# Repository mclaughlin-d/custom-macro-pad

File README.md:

# custom-macro-pad
This repo has a pretty simple PCB I made a while back, just to familiarize myself with KiCad. 
Here are some photos!

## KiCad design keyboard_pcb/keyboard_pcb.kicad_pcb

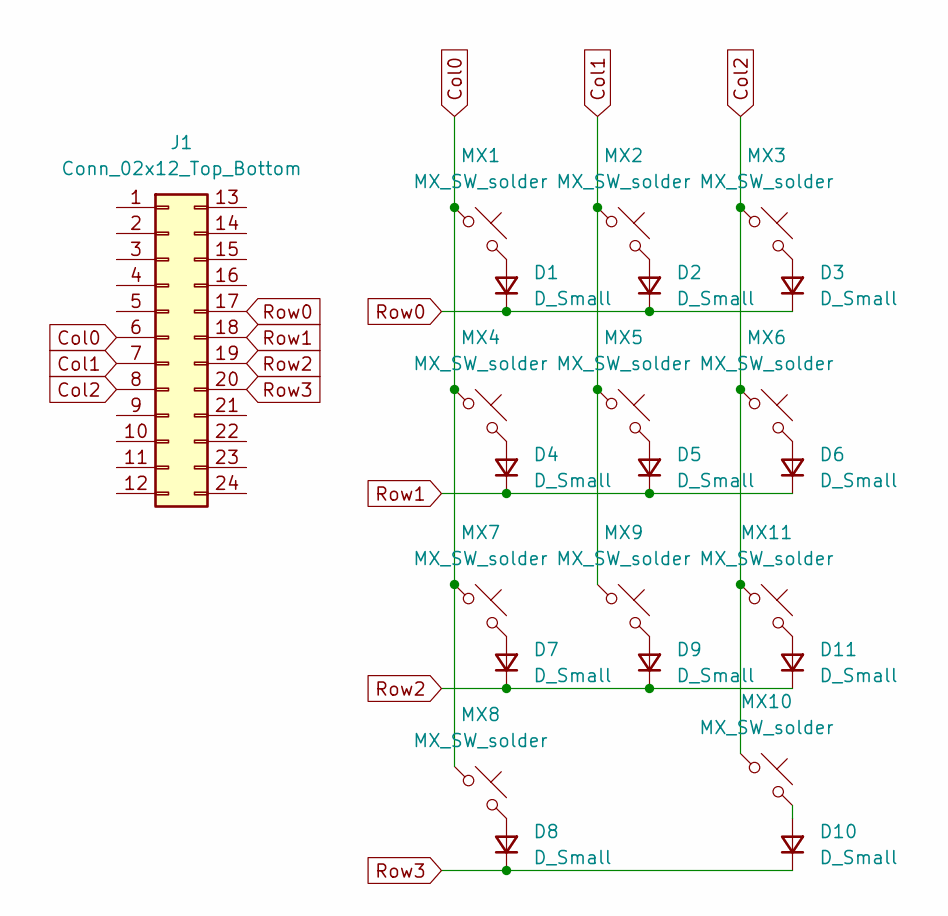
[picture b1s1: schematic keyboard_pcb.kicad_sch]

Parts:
D1, D2, D3, D4, D5, D6, D7, D8, D9, D10, D11: D_Small; D_SOD-123
J1: Conn_02x12_Top_Bottom; ProMicro_USBup
MX1, MX2, MX3, MX4, MX5, MX6, MX7, MX9, MX11: MX_SW_solder; SW_MX_1u
MX8, MX10: MX_SW_solder; SW_MX_1.5u

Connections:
Col0: J1.6, MX1.1, MX4.1, MX7.1, MX8.1
Col1: J1.7, MX2.1, MX5.1, MX9.1
Col2: J1.8, MX3.1, MX6.1, MX10.1, MX11.1
unnamed: D1.2 (A), MX1.2
unnamed: D2.2 (A), MX2.2
unnamed: D3.2 (A), MX3.2
unnamed: D4.2 (A), MX4.2
unnamed: D5.2 (A), MX5.2
unnamed: D6.2 (A), MX6.2
unnamed: D7.2 (A), MX7.2
unnamed: D8.2 (A), MX8.2
unnamed: D9.2 (A), MX9.2
unnamed: D10.2 (A), MX10.2
unnamed: D11.2 (A), MX11.2
Row0: D1.1 (K), D2.1 (K), D3.1 (K), J1.17
Row1: D4.1 (K), D5.1 (K), D6.1 (K), J1.18
Row2: D7.1 (K), D9.1 (K), D11.1 (K), J1.19
Row3: D8.1 (K), D10.1 (K), J1.20

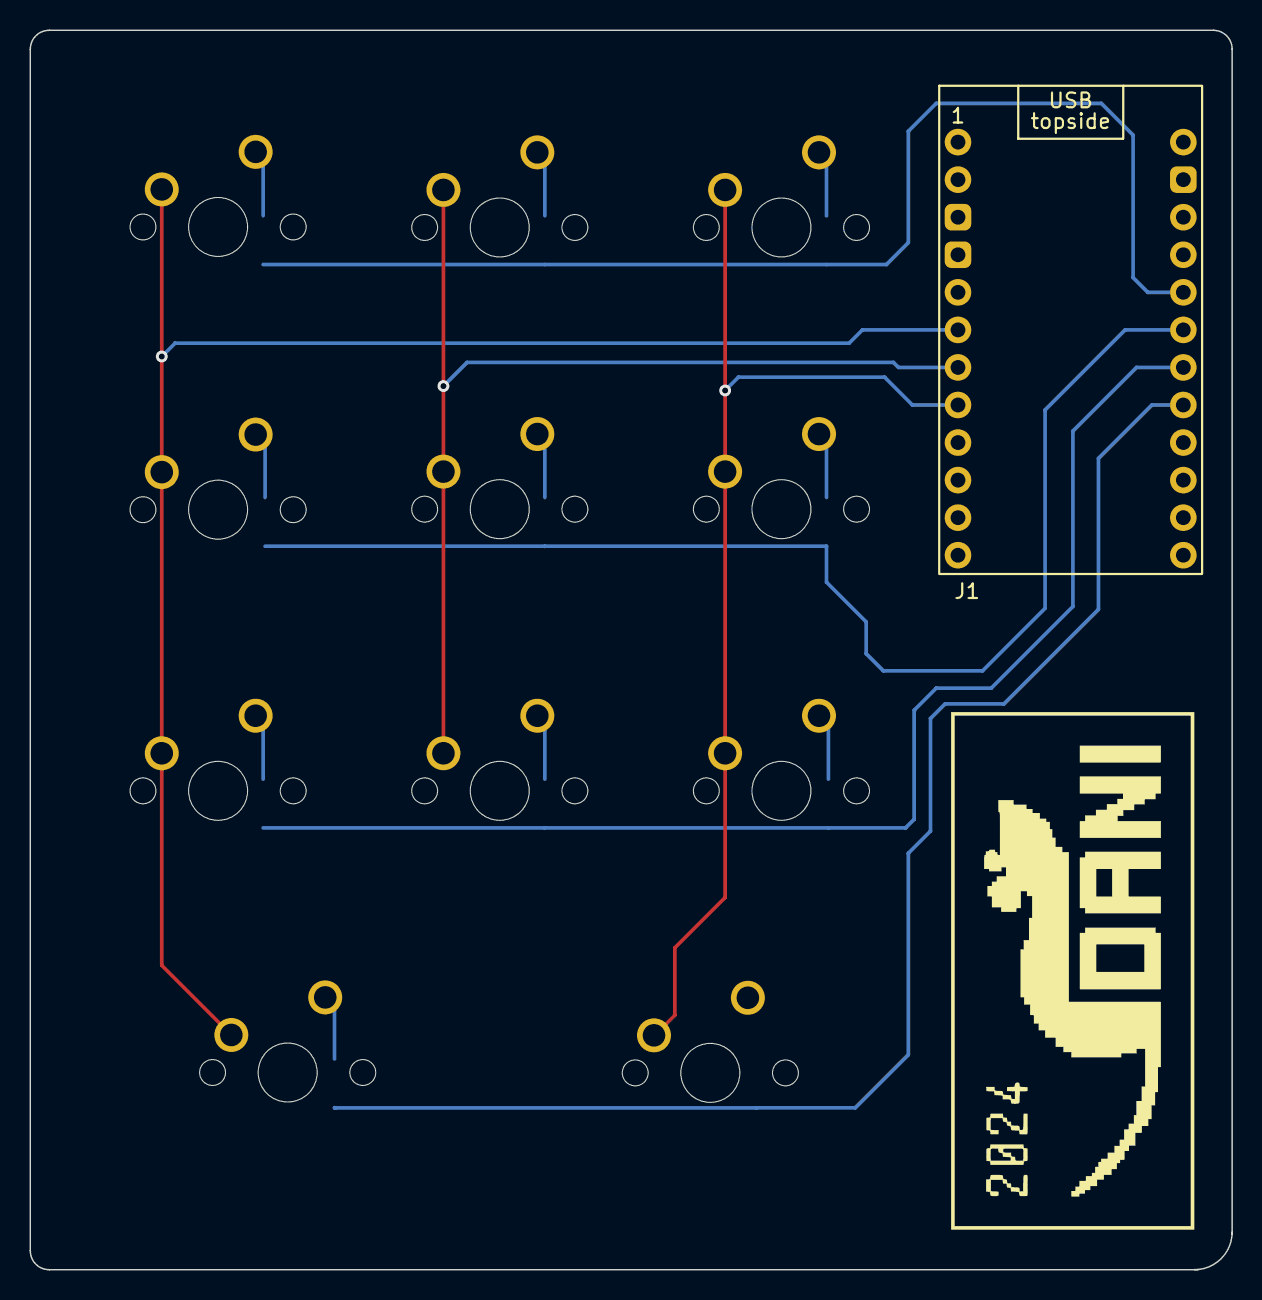
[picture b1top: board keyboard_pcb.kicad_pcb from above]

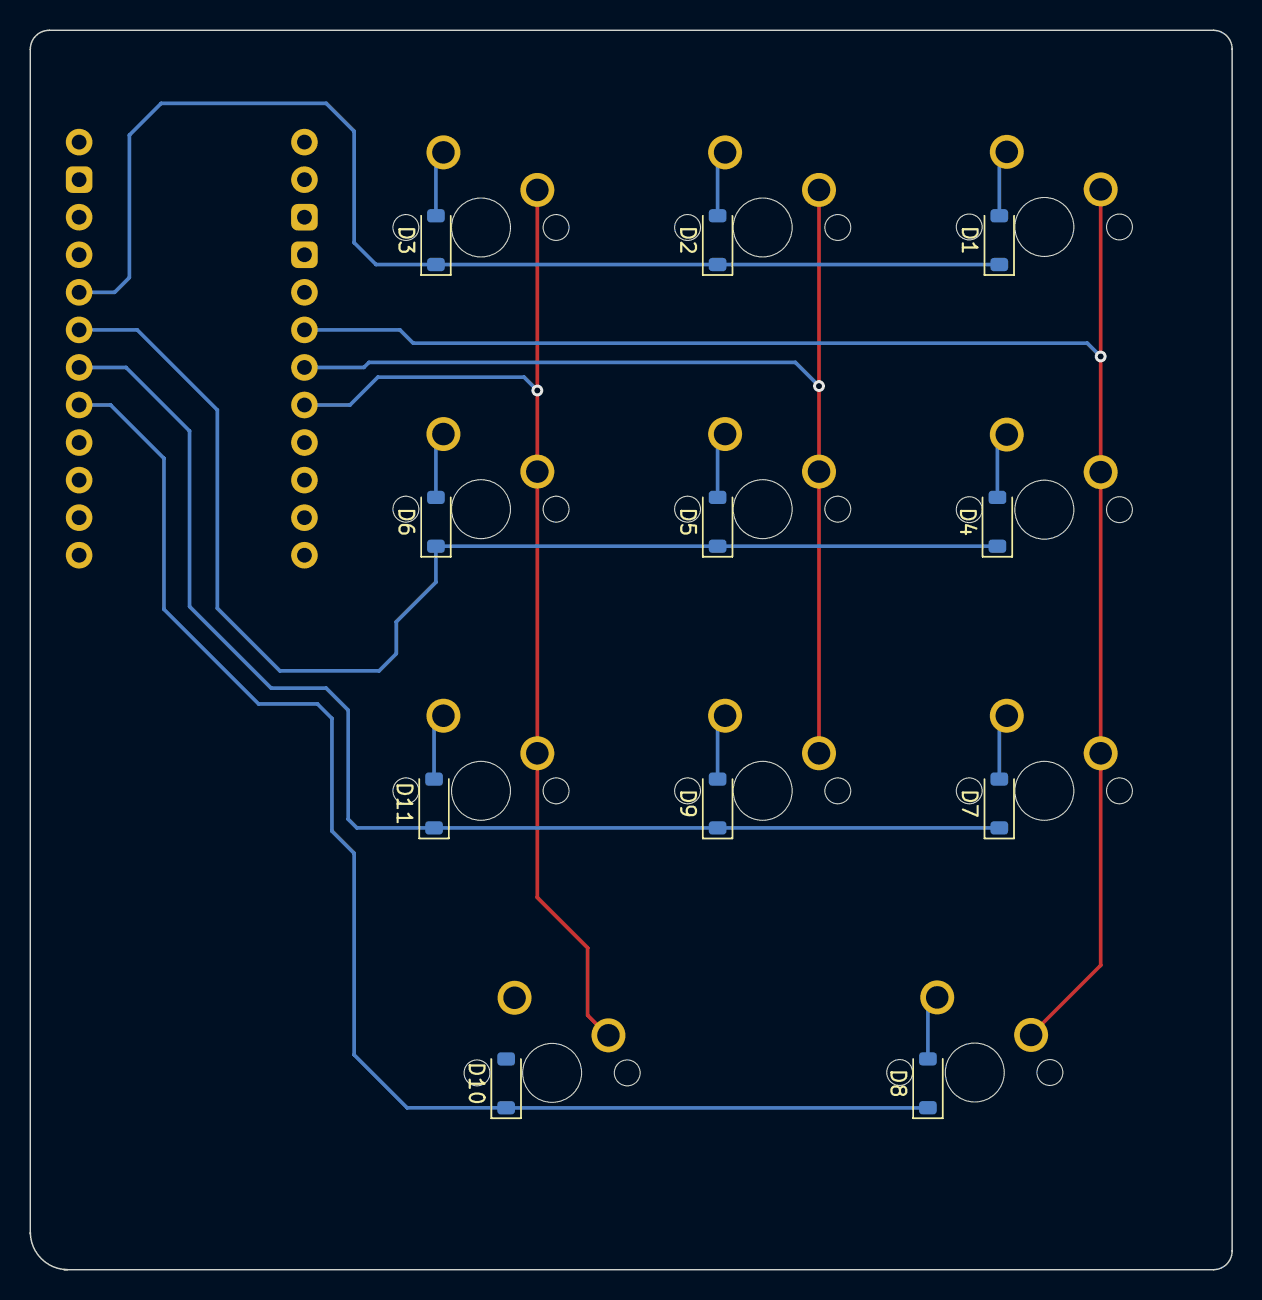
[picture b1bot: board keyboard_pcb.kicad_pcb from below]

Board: 2 copper layers, 81.3 x 83.8 mm, 24 parts (11 on the bottom side), 18 nets.

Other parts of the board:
Logo: LOGO; black_logo

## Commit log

2024-03-28 add KiCad documents
